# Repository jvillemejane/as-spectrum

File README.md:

# Arts et Sciences Project
2023-2024

This is a test.

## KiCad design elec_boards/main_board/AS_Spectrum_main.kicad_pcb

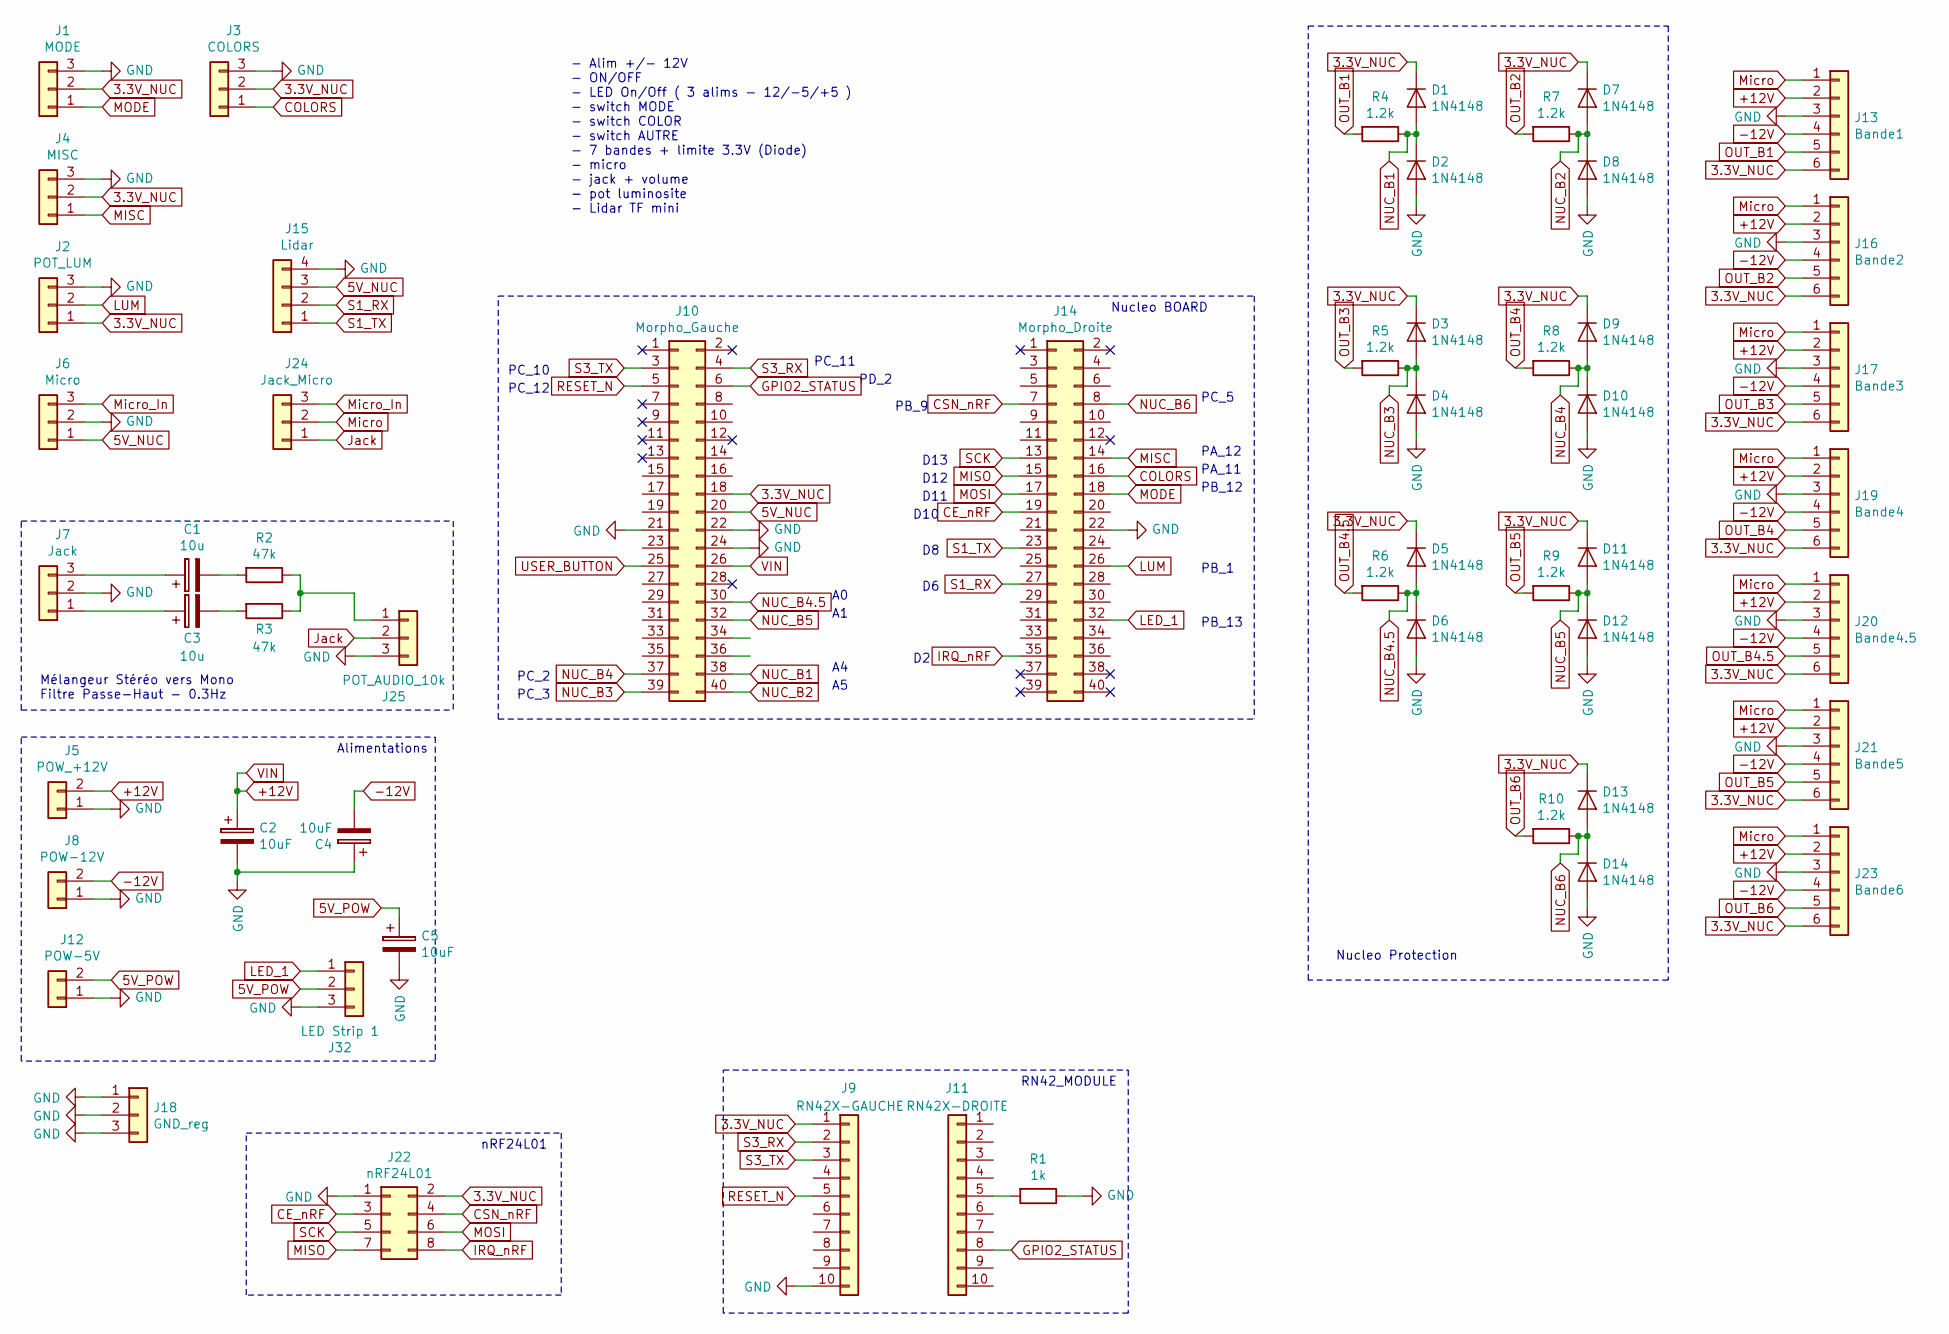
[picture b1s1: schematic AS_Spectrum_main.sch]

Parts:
C1, C3: 10u; CP_Radial_D10.0mm_P5.00mm
C2, C4, C5: 10uF; CP_Radial_D10.0mm_P5.00mm
D1, D2, D3, D4, D5, D6, D7, D8, D9, D10, D11, D12, D13, D14: 1N4148; D_DO-35_SOD27_P7.62mm_Horizontal
J1: MODE; PinSocket_1x03_P2.54mm_Vertical
J2: POT_LUM; PinSocket_1x03_P2.54mm_Vertical
J3: COLORS; PinSocket_1x03_P2.54mm_Vertical
J4: MISC; PinSocket_1x03_P2.54mm_Vertical
J5: POW_+12V; TerminalBlock_Phoenix_MKDS-3-2-5.08_1x02_P5.08mm_Horizontal
J6: Micro; PinSocket_1x03_P2.54mm_Vertical
J7: Jack; PinSocket_1x03_P2.54mm_Vertical
J8: POW-12V; TerminalBlock_Phoenix_MKDS-3-2-5.08_1x02_P5.08mm_Horizontal
J9: RN42X-GAUCHE; PinHeader_1x10_P2.00mm_Vertical
J10: Morpho_Gauche; PinHeader_2x20_P2.54mm_Vertical
J11: RN42X-DROITE; PinHeader_1x10_P2.00mm_Vertical
J12: POW-5V; TerminalBlock_Phoenix_MKDS-3-2-5.08_1x02_P5.08mm_Horizontal
J13: Bande1; PinSocket_1x06_P2.54mm_Horizontal
J14: Morpho_Droite; PinHeader_2x20_P2.54mm_Vertical
J15: Lidar; PinSocket_1x04_P2.54mm_Vertical
J16: Bande2; PinSocket_1x06_P2.54mm_Horizontal
J17: Bande3; PinSocket_1x06_P2.54mm_Horizontal
J18: GND_reg; PinHeader_1x03_P2.54mm_Vertical
J19: Bande4; PinSocket_1x06_P2.54mm_Horizontal
J20: Bande4.5; PinSocket_1x06_P2.54mm_Horizontal
J21: Bande5; PinSocket_1x06_P2.54mm_Horizontal
J22: nRF24L01; PinHeader_2x04_P2.54mm_Vertical
J23: Bande6; PinSocket_1x06_P2.54mm_Horizontal
J24: Jack_Micro; PinSocket_1x03_P2.54mm_Vertical
J25: POT_AUDIO_10k; PinSocket_1x03_P2.54mm_Vertical
J32: LED Strip 1; PinSocket_1x03_P2.54mm_Vertical
R1: 1k; R_Axial_DIN0207_L6.3mm_D2.5mm_P10.16mm_Horizontal
R2, R3: 47k; R_Axial_DIN0207_L6.3mm_D2.5mm_P10.16mm_Horizontal
R4, R5, R6, R7, R8, R9, R10: 1.2k; R_Axial_DIN0207_L6.3mm_D2.5mm_P10.16mm_Horizontal

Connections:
3.3V_NUC: D1.1 (K), D3.1 (K), D5.1 (K), D7.1 (K), D9.1 (K), D11.1 (K), D13.1 (K), J1.2, J2.1, J3.2, J4.2, J9.1, J10.18, J13.6, J16.6, J17.6, J19.6, J20.6, J21.6, J22.2, J23.6
5V_NUC: J6.1, J10.20, J15.3
5V_POW: C5.1, J12.2, J32.2; also elsewhere on the board
+12V: C2.1, J5.2, J10.26, J13.2, J16.2, J17.2, J19.2, J20.2, J21.2, J23.2; also elsewhere on the board
-12V: C4.2, J8.2, J13.4, J16.4, J17.4, J19.4, J20.4, J21.4, J23.4; also elsewhere on the board
CE_nRF: J14.19, J22.3
COLORS: J3.1, J14.16
CSN_nRF: J14.7, J22.4
GND: C2.2, C4.1, C5.2, D2.2 (A), D4.2 (A), D6.2 (A), D8.2 (A), D10.2 (A), D12.2 (A), D14.2 (A), J1.3, J2.3, J3.3, J4.3, J5.1, J6.2, J7.2, J8.1, J9.10, J10.21, J10.22, J10.24, J12.1, J13.3, J14.22, J15.4, J16.3, J17.3, J18.1, J18.2, J18.3, J19.3, J20.3, J21.3, J22.1, J23.3, J25.3, J32.3, R1.1; also elsewhere on the board
GPIO2_STATUS: J10.6, J11.8
IRQ_nRF: J14.35, J22.8
Jack: J24.1, J25.2
LED_1: J14.32, J32.1
LUM: J2.2, J14.26
MISC: J4.1, J14.14
MISO: J14.15, J22.7
MODE: J1.1, J14.18
MOSI: J14.17, J22.6
Micro: J13.1, J16.1, J17.1, J19.1, J20.1, J21.1, J23.1, J24.2
Micro_In: J6.3, J24.3
NUC_B1: D1.2 (A), D2.1 (K), J10.38, R4.1
NUC_B2: D7.2 (A), D8.1 (K), J10.40, R7.1
NUC_B3: D3.2 (A), D4.1 (K), J10.39, R5.1
NUC_B4: D9.2 (A), D10.1 (K), J10.37, R8.1
NUC_B4.5: D5.2 (A), D6.1 (K), J10.30, R6.1
NUC_B5: D11.2 (A), D12.1 (K), J10.32, R9.1
NUC_B6: D13.2 (A), D14.1 (K), J14.8, R10.1
unnamed: C1.1, J7.3
unnamed: C1.2, R2.2
unnamed: C3.1, J7.1
unnamed: C3.2, R3.2
unnamed: J11.5, R1.2
unnamed: J25.1, R2.1, R3.1
OUT_B1: J13.5, R4.2
OUT_B2: J16.5, R7.2
OUT_B3: J17.5, R5.2
OUT_B4: J19.5, R8.2
OUT_B4.5: J20.5, R6.2
OUT_B5: J21.5, R9.2
OUT_B6: J23.5, R10.2
RESET_N: J9.5, J10.5
S1_RX: J14.27, J15.2
S1_TX: J14.23, J15.1
S3_RX: J9.2, J10.4
S3_TX: J9.3, J10.3
SCK: J14.13, J22.5
USER_BUTTON: J10.25

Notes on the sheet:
RN42_MODULE
Nucleo BOARD
- Alim +/- 12V - ON/OFF - LED On/Off ( 3 alims - 12/-5/+5 ) - switch MODE - switch COLOR - switch AUTRE - 7 bandes + limite 3.3V (Diode) - micro - jack + volume - pot luminosite - Lidar TF mini
Mélangeur Stéréo vers Mono Filtre Passe-Haut - 0.3Hz
Alimentations
nRF24L01
Nucleo Protection
PC_5
PC_3
PC_2
PA_12
PA_11
PB_12
D13
D12
D11
PC_10
PC_12
PC_11
PD_2
PB_13
PB_1
PB_9
D10

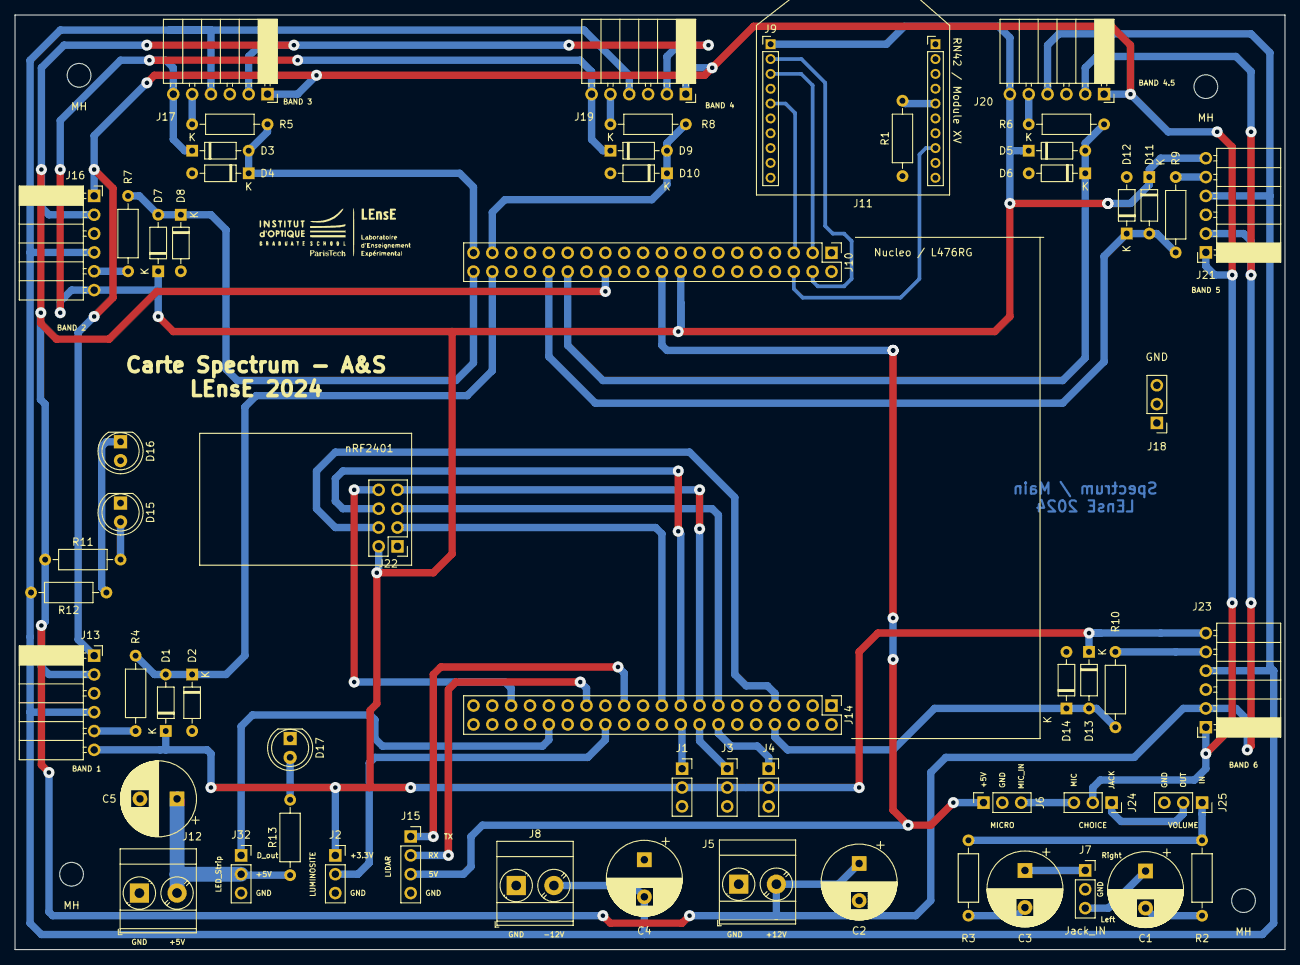
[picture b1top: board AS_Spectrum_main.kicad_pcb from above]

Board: 2 copper layers, 171.2 x 126.0 mm, 65 parts (0 on the bottom side), 49 nets.

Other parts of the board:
D15: LED_12V; LED_D5.0mm_FlatTop
D16: LED_-12V; LED_D5.0mm_FlatTop
D17: LED_5V; LED_D5.0mm_FlatTop
MH: MountingHole_3.2mm_M3
MH#2, MH#3, MH#4: MountingHole_3.2mm_M3
R11, R12: 560; R_Axial_DIN0207_L6.3mm_D2.5mm_P10.16mm_Horizontal
R13: 220; R_Axial_DIN0207_L6.3mm_D2.5mm_P10.16mm_Horizontal

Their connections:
5V_POW: R13.1; also elsewhere on the board
+12V: R11.1; also elsewhere on the board
-12V: R12.2; also elsewhere on the board
GND: D15.1, D16.2, D17.1; also elsewhere on the board
unnamed: D15.2, R11.2
unnamed: D16.1, R12.1
unnamed: D17.2, R13.2

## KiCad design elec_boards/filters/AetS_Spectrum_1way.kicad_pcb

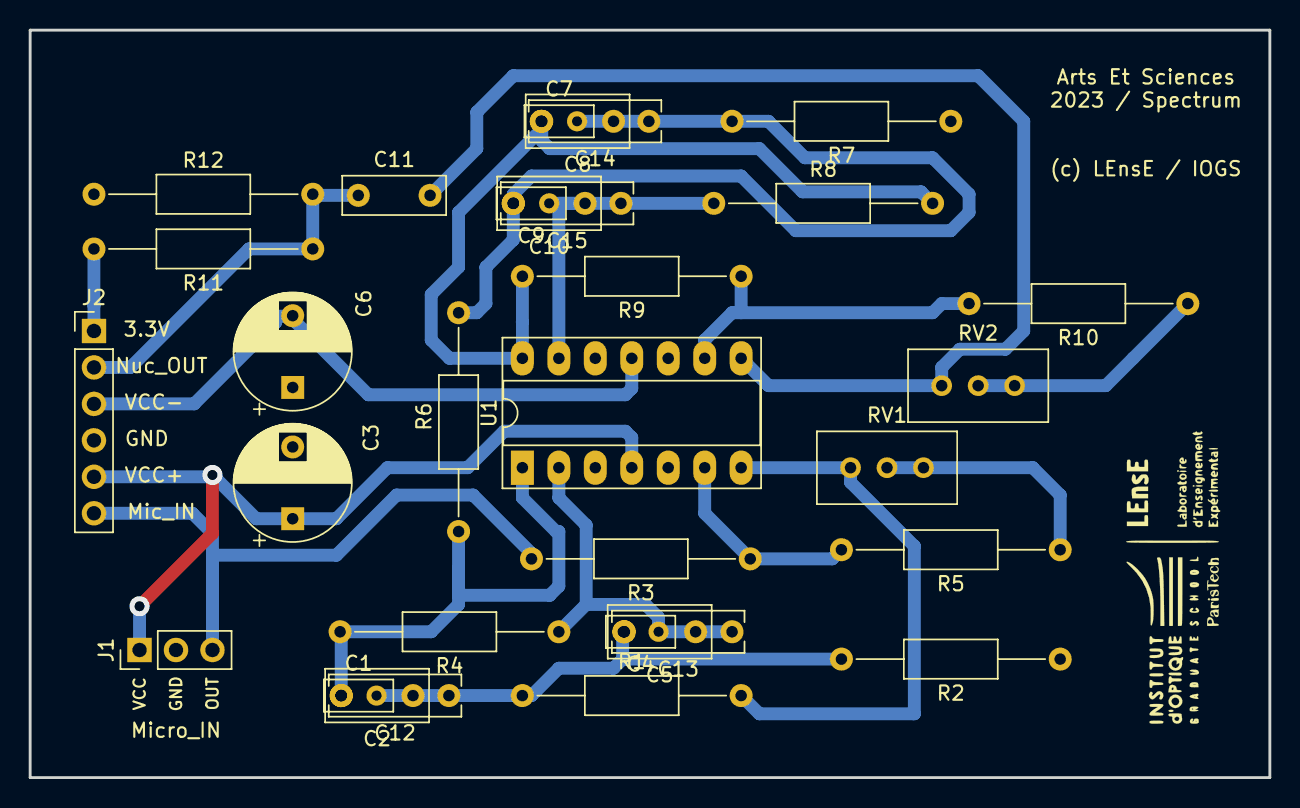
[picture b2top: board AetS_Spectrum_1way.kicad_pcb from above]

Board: 2 copper layers, 86.4 x 52.1 mm, 32 parts (0 on the bottom side), 18 nets.

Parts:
C1, C4, C7, C9: C; C_Rect_L4.6mm_W2.0mm_P2.50mm_MKS02_FKP02
C2, C5, C8, C10: C; C_Rect_L7.0mm_W3.5mm_P5.00mm
C3, C6: 100uF; CP_Radial_D8.0mm_P5.00mm
C11: 100nF; C_Rect_L7.0mm_W2.5mm_P5.00mm
C12, C13, C14, C15: C; C_Rect_L9.0mm_W2.7mm_P7.50mm_MKT
J1: Micro_test; PinHeader_1x03_P2.54mm_Vertical
J2: Conn_01x06; PinHeader_1x06_P2.54mm_Vertical
R1, R2, R4, R6, R7, R8: R; R_Axial_DIN0207_L6.3mm_D2.5mm_P15.24mm_Horizontal
R3, R9: 10k; R_Axial_DIN0207_L6.3mm_D2.5mm_P15.24mm_Horizontal
R5, R10: 1k; R_Axial_DIN0207_L6.3mm_D2.5mm_P15.24mm_Horizontal
R11, R12: 180k; R_Axial_DIN0207_L6.3mm_D2.5mm_P15.24mm_Horizontal
RV1, RV2: 100k; Potentiometer_Bourns_3296W_Vertical
U1: TL084; DIP-14_W7.62mm_Socket_LongPads

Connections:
3.3V: J2.1, R11.2
GND: C3.2, C6.1, J1.2, J2.4, R2.1, R7.1, R12.1, U1.3, U1.5, U1.10, U1.12
In_Nuc_B1: C11.1, J2.2, R11.1, R12.2
unnamed: C1.1, C2.2, C12.2, R4.2, R6.2, U1.1
unnamed: C1.2, C2.1, C4.2, C5.2, C12.1, C13.2, R1.1, R2.2
unnamed: C9.1, C10.1, C15.1, R8.1, U1.13
unnamed: C7.2, C8.1, C9.2, C10.2, C14.1, C15.2, R6.1, R7.2
unnamed: C4.1, C5.1, C13.1, R4.1, U1.2
unnamed: R3.1, R5.2, U1.6
unnamed: R5.1, RV1.1, RV1.2
unnamed: R10.1, RV2.1, RV2.2
unnamed: R9.1, R10.2, U1.9
Out_B1: C11.2, RV2.3, U1.8
Out_Filtre: C7.1, C8.2, C14.2, R8.2, R9.2, U1.14
VCC+: C3.1, J1.1, J2.5, U1.4
VCC-: C6.2, J2.3, U1.11
Vin_micro: J1.3, J2.6, R3.2
Vout_micro: R1.2, RV1.3, U1.7

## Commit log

2024-02-14 Update Schematic Main Board
2024-02-14 Update Main Board Schematic and PCB
2024-02-15 Update Schematics and PCB
2024-02-15 Update Schematics and PCB - Adding LEDs
2024-02-15 Update PCB
2024-05-01 Adding program with mode selection
2024-05-01 Update Mode selection program
2024-05-02 Adding filters characterization and demo test
2024-05-02 Update Test program (Fading, Sound, Analyzer)
2024-05-31 Adding poster
2024-05-31 Update Poster
2024-06-11 Update Boitier
2024-06-19 Add programs MBED
